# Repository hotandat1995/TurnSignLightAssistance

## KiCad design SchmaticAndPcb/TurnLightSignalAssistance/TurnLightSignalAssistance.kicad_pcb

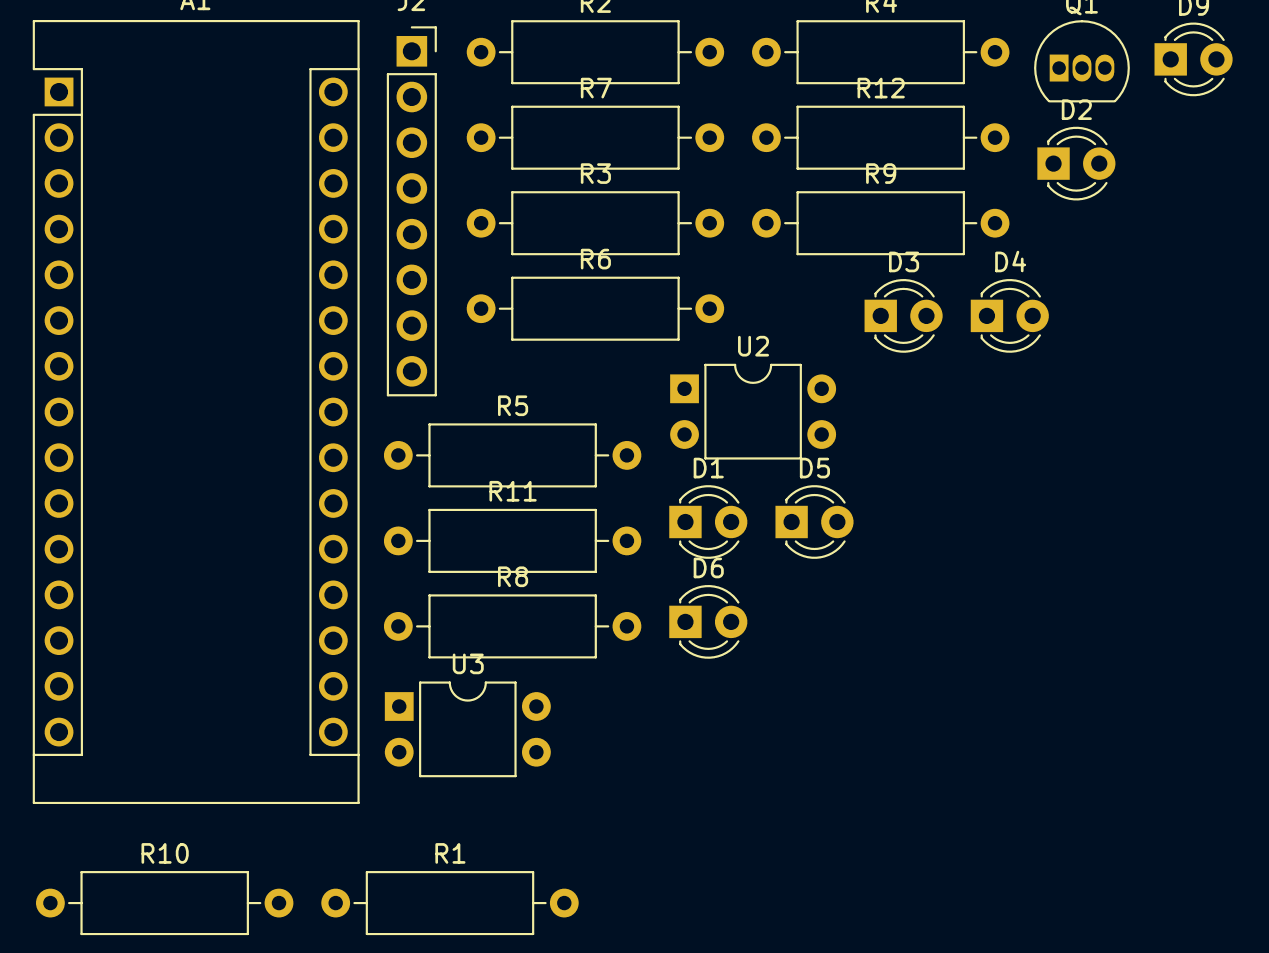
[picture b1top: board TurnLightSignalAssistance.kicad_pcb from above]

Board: 2 copper layers, 24 parts (0 on the bottom side), 21 nets, no tracks yet.

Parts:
A1: Arduino_Nano_v3.x; Arduino_Nano
D1, D2, D3, D4, D5, D6, D9: LED; LED_D3.0mm
J2: MPU6050; PinSocket_1x08_P2.54mm_Vertical
Q1: 2SC1815; TO-92_Inline
R1, R2, R3, R4, R5, R6, R7, R8, R9, R10: 1K; R_Axial_DIN0309_L9.0mm_D3.2mm_P12.70mm_Horizontal
R11: 10K; R_Axial_DIN0309_L9.0mm_D3.2mm_P12.70mm_Horizontal
R12: 220; R_Axial_DIN0309_L9.0mm_D3.2mm_P12.70mm_Horizontal
U2, U3: PC817; DIP-4_W7.62mm

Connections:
+5V: J2.1, R9.2, R10.2
-BATT: U2.2, U3.2
/AliveLed: A1.12 (D9), R12.2
/BlinkLeft: R2.2, R3.2, R4.2, R5.2
/BlinkRight: R1.2, R6.1, R7.1, R8.1
/LedBlinkGnd: D1.1 (K), D2.1 (K), D3.1 (K), D4.1 (K), D5.1 (K), D6.1 (K)
/SCL: A1.24 (A5), J2.3
/SDA: A1.23 (A4), J2.4
/SignalLeft: A1.14 (D11), R10.1, U3.4
/SignalRight: A1.13 (D10), R9.1, U2.4
GND: A1.4 (GND), A1.29 (GND), D9.1 (K), J2.2, Q1.1 (E), U2.3, U3.3
unnamed: D1.2 (A), R3.1
unnamed: D2.2 (A), R4.1
unnamed: D3.2 (A), R5.1
unnamed: D4.2 (A), R6.2
unnamed: D5.2 (A), R7.2
unnamed: D6.2 (A), R8.2
unnamed: D9.2 (A), R12.1
unnamed: R1.1, U2.1
unnamed: R2.1, U3.1
unnamed: Q1.3 (B), R11.1

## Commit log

2022-05-22 first step: Get the value from MPU6050
2022-05-24 support monitoring data from MUP6050 in PC
2022-06-05 update schematic and component
2022-06-05 remove component
2022-06-14 Fix the schematic
2022-06-19 fixing and optimizing schematic
2022-06-27 update document and fix schematic
2022-06-27 Separate the simulate part and main part. Update the document
2022-06-28 Update source code move it to it own folder
2022-06-28 update DataControl to work on the board
2022-06-28 Added the file description and the include guard for DataControl.h
2022-06-29 update state machine
2022-07-01 Update the patent document
2022-07-02 The state machine is working, remove the display due to not enough RAM
2022-08-16 Update the workspace configure
2022-09-05 update the angle check
2022-09-06 fix the error when change wrong side
